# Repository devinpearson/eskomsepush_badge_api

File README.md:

# Eskomsepush status badge

This is a fun project to create a physical repesentation of the loadshedding schedule. its still a work in progress and open to suggestions or improvements.

### Installation
Before installing, [download and install Node.js](https://nodejs.org/en/download/).

```bash
git clone https://github.com/devinpearson/eskomsepush_badge_api.git
cd eskomsepush_badge_api
```
```bash
npm install
```

### Usage
To start the server, run the following
```bash
npm start
```

This will start the simulator on http://localhost:3000

### badge setup
The badge requires a firebeetle esp32 module. The firmware can be found in board/sketch. you will need to set your wifi details.

### badge pcb files
The badge files are present if anyone wants to make changes or send them off to a pcb fab. JLCPCB is a great option.

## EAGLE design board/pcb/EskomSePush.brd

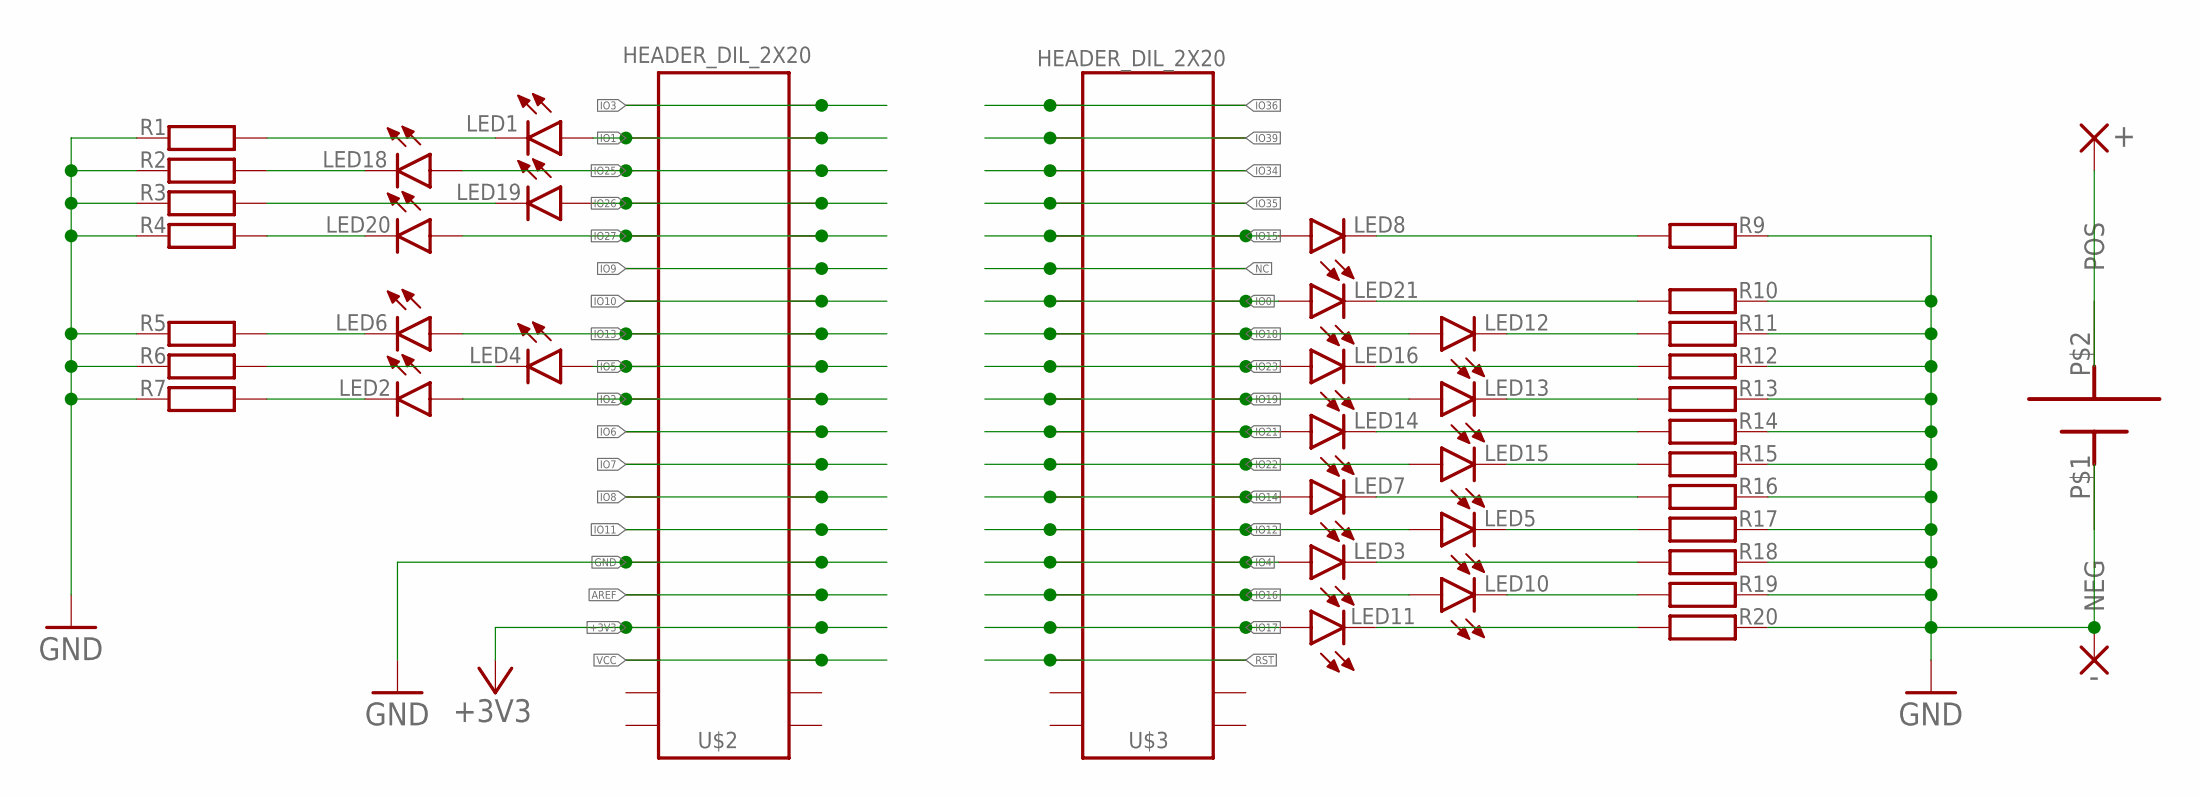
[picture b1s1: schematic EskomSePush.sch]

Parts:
+: WIREPADSMD2,54-5,08; SMD2,54-5,08
-: WIREPADSMD2,54-5,08; SMD2,54-5,08
LED1, LED2, LED3, LED4, LED5, LED6, LED7, LED8, LED10, LED11, LED12, LED13, LED14, LED15, LED16, LED18, LED19, LED20, LED21: LEDCHIPLED_1206; CHIPLED_1206
R1, R2, R3, R4, R5, R6, R7, R9, R10, R11, R12, R13, R14, R15, R16, R17, R18, R19, R20: R-EU_R1206; R1206
U$1: 21700BATTERYHOLDER
U$2, U$3: HEADER_DIL_2X20

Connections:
+3V3: U$2.P$17, U$2.P$37
AREF: U$2.P$16, U$2.P$36
GND: -.1, R1.1, R2.1, R3.1, R4.1, R5.1, R6.1, R7.1, R9.2, R10.2, R11.2, R12.2, R13.2, R14.2, R15.2, R16.2, R17.2, R18.2, R19.2, R20.2, U$1.P$1 (NEG), U$2.P$15, U$2.P$35
IO0: LED21.A, U$3.P$7, U$3.P$27
IO1: LED1.A, U$2.P$2, U$2.P$22
IO2: LED2.A, U$2.P$10, U$2.P$30
IO3: U$2.P$1, U$2.P$21
IO4: LED3.A, U$3.P$15, U$3.P$35
IO5: LED4.A, U$2.P$9, U$2.P$29
IO6: U$2.P$11, U$2.P$31
IO7: U$2.P$12, U$2.P$32
IO8: U$2.P$13, U$2.P$33
IO9: U$2.P$6, U$2.P$26
IO10: U$2.P$7, U$2.P$27
IO11: U$2.P$14, U$2.P$34
IO12: LED5.A, U$3.P$14, U$3.P$34
IO13: LED6.A, U$2.P$8, U$2.P$28
IO14: LED7.A, U$3.P$13, U$3.P$33
IO15: LED8.A, U$3.P$5, U$3.P$25
IO16: LED10.A, U$3.P$16, U$3.P$36
IO17: LED11.A, U$3.P$17, U$3.P$37
IO18: LED12.A, U$3.P$8, U$3.P$28
IO19: LED13.A, U$3.P$10, U$3.P$30
IO21: LED14.A, U$3.P$11, U$3.P$31
IO22: LED15.A, U$3.P$12, U$3.P$32
IO23: LED16.A, U$3.P$9, U$3.P$29
IO25: LED18.A, U$2.P$3, U$2.P$23
IO26: LED19.A, U$2.P$4, U$2.P$24
IO27: LED20.A, U$2.P$5, U$2.P$25
IO34: U$3.P$3, U$3.P$23
IO35: U$3.P$4, U$3.P$24
IO36: U$3.P$1, U$3.P$21
IO39: U$3.P$2, U$3.P$22
unnamed: LED1.C, R1.2
unnamed: LED18.C, R2.2
unnamed: LED19.C, R3.2
unnamed: LED20.C, R4.2
unnamed: LED4.C, R6.2
unnamed: LED2.C, R7.2
unnamed: LED6.C, R5.2
unnamed: LED8.C, R9.1
unnamed: LED21.C, R10.1
unnamed: LED12.C, R11.1
unnamed: LED16.C, R12.1
unnamed: LED13.C, R13.1
unnamed: LED14.C, R14.1
unnamed: LED15.C, R15.1
unnamed: LED5.C, R17.1
unnamed: LED7.C, R16.1
unnamed: LED3.C, R18.1
unnamed: LED10.C, R19.1
unnamed: LED11.C, R20.1
unnamed: +.1, U$1.P$2 (POS)
NC: U$3.P$6, U$3.P$26
RST: U$3.P$18, U$3.P$38
VCC: U$2.P$18, U$2.P$38

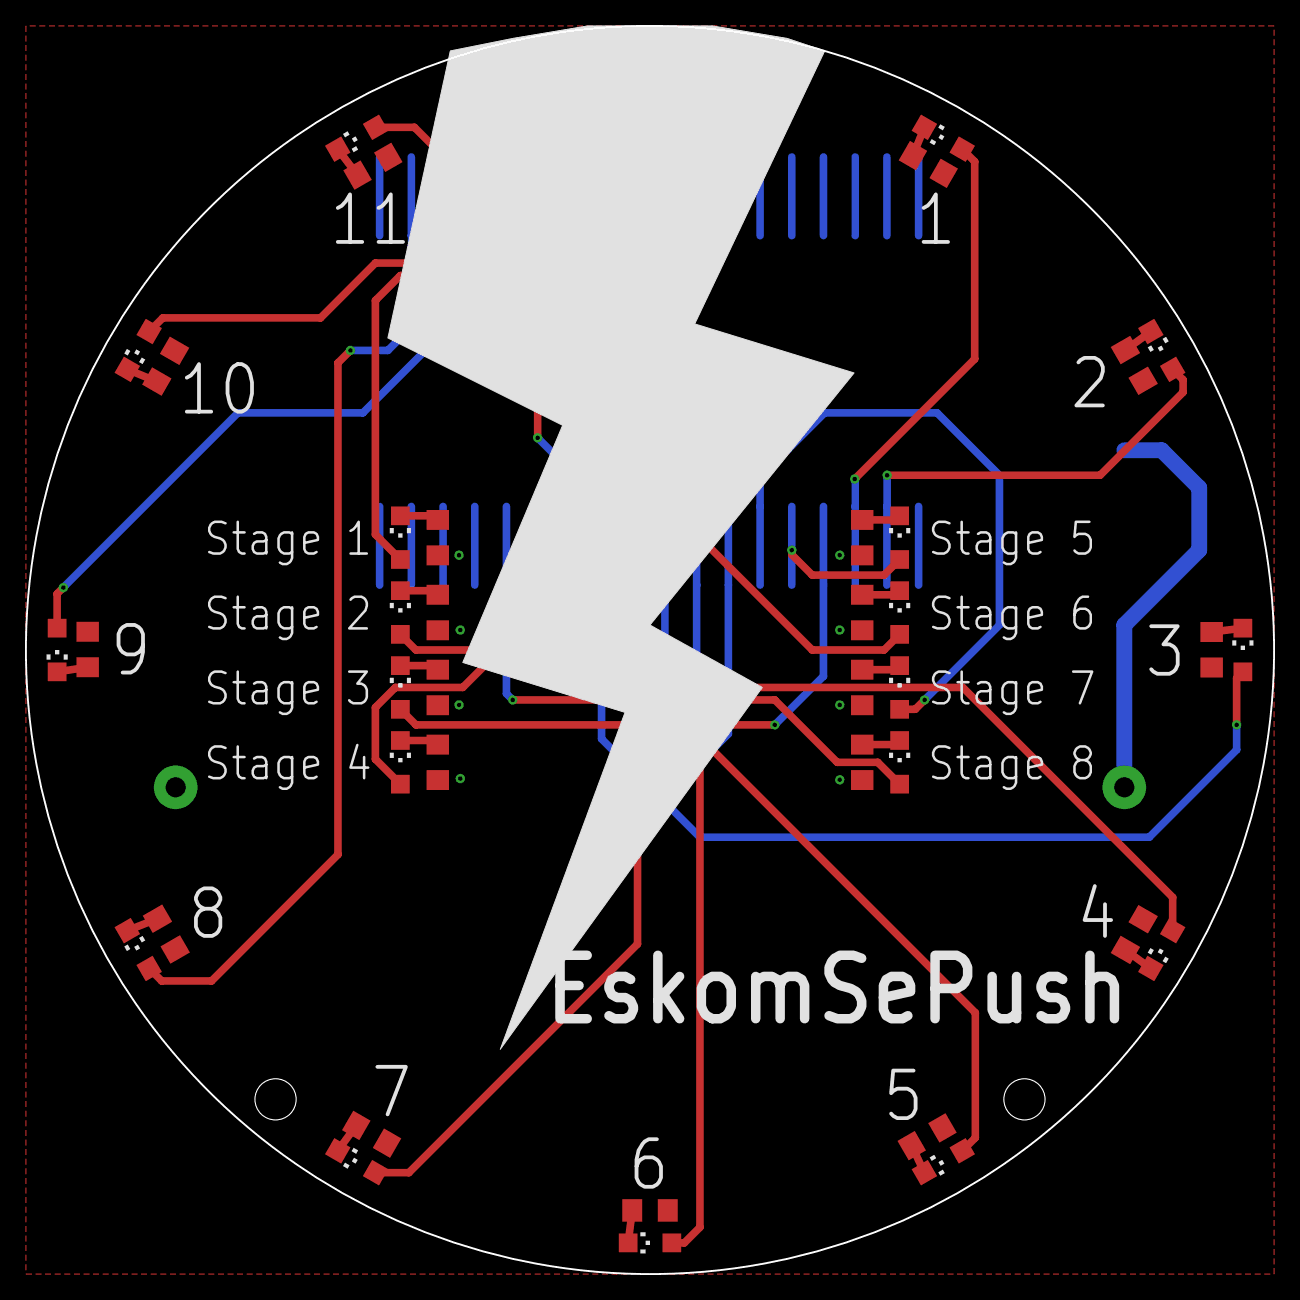
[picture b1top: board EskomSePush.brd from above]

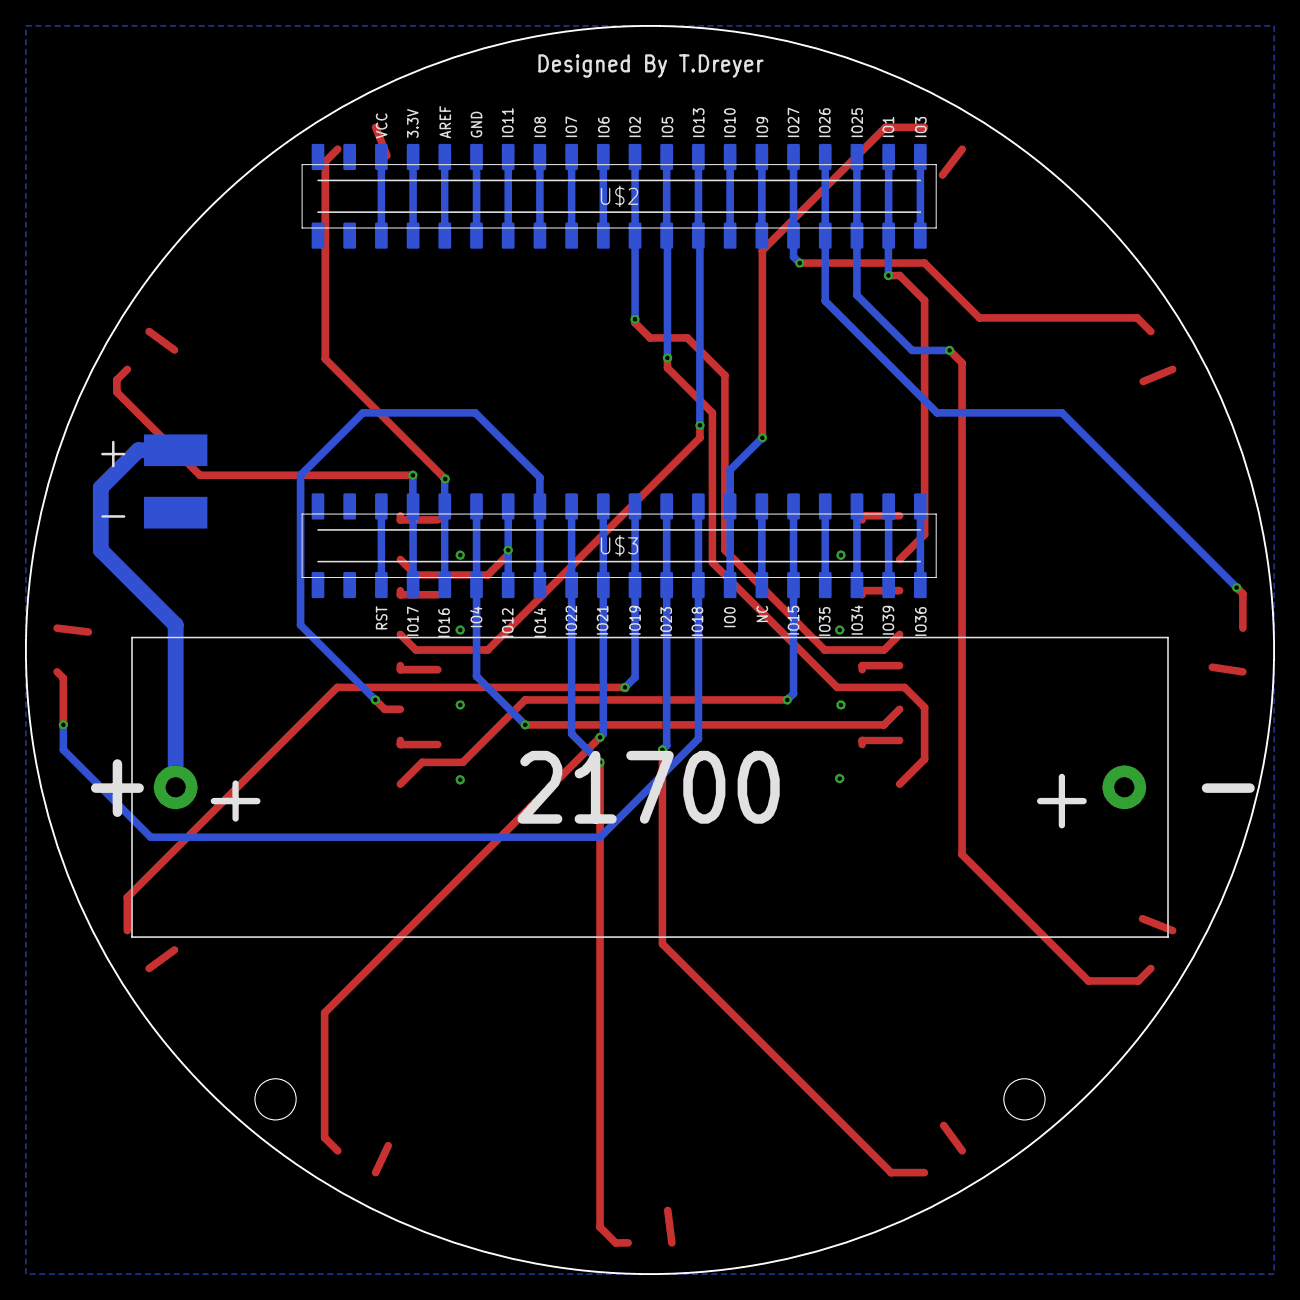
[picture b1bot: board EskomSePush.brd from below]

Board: 2 copper layers, 100.0 x 100.0 mm, 43 parts (5 on the bottom side), 56 nets.

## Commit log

2022-10-17 added nodemon and start script
2022-10-17 Added board files and sketch
2022-10-17 added readme and license
2022-10-17 add digital ocean template
2022-10-18 updated to v2 of the led selection
2022-10-18 Added additional calculations for time till loadshedding
2022-10-18 testing out env variables
